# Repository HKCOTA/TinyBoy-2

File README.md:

# TinyBoy(TM) 2
A 3D Printer for Kids.

This repo are stored all the Blue Prints and design diagrams.
The TinyBoy design comes ABSOLUTELY NO WARRANTY!

[TinyBoy(TM) 2](http://www.tinyboy.net) by [Hong Kong Creative Open Technology Association (HKCOTA)](http://cota.hk), blueprints and designs are licensed under a Creative Commons Attribution-NonCommercial-ShareAlike 4.0 International (CC BY-NC-SA 4.0).
  
To view a copy of this license, visit [https://creativecommons.org/licenses/by-nc-sa/4.0/legalcode](https://creativecommons.org/licenses/by-nc-sa/4.0/legalcode). 

# You are free to:

* Share — copy and redistribute the material in any medium or format
* Adapt — remix, transform, and build upon the material 

# Under the following terms:

* Attribution — You must give appropriate credit, provide a link to the license, and indicate if changes were made. You may do so in any reasonable manner, but not in any way that suggests the licensor endorses you or your use.

* NonCommercial — You may not use the material for commercial purposes.

* ShareAlike — If you remix, transform, or build upon the material, you must distribute your contributions under the same license as the original. 

# TinyBoy Projects are also using the hardware and firmware from the following projects:

## Melzi Projects, For L10/L16
* using MKS's Melzi clone board, SMELZI, which should be license under GPL 2.0. MKS said it is possible to get the board design if you ask them. But we have doubt on it.
The printers produced by MakeOmnia Ltd would still use this board. 

## RMAPS v1.4, For Lite/J10
* which is license under GPL. As HKCOTA have doubt on the board, so for the HKCOTA version, we choose to use RAMPS v1.4 + Arduino as the main board of the printer.

## Marlin Firmware project
* which is license under GPL. You can get the forked source from [https://github.com/wanleung/Marlin-TinyBoy/](https://github.com/wanleung/Marlin-TinyBoy/).

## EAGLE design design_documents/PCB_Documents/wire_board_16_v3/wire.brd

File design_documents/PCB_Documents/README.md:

# TinyBoy(TM) 2
A 3D Printer for Kids.

This repo are stored all the Blue Prints and design diagrams.
The TinyBoy design comes ABSOLUTELY NO WARRANTY!

[TinyBoy(TM) 2](http://www.tinyboy.net) by [Hong Kong Creative Open Technology Association (HKCOTA)](http://cota.hk) is licensed under a Creative Commons Attribution-NonCommercial-ShareAlike 4.0 International (CC BY-NC-SA 4.0).
  
To view a copy of this license, visit [https://creativecommons.org/licenses/by-nc-sa/4.0/legalcode](https://creativecommons.org/licenses/by-nc-sa/4.0/legalcode). 

# You are free to:

* Share — copy and redistribute the material in any medium or format
* Adapt — remix, transform, and build upon the material 

# Under the following terms:

* Attribution — You must give appropriate credit, provide a link to the license, and indicate if changes were made. You may do so in any reasonable manner, but not in any way that suggests the licensor endorses you or your use.

* NonCommercial — You may not use the material for commercial purposes.

* ShareAlike — If you remix, transform, or build upon the material, you must distribute your contributions under the same license as the original.

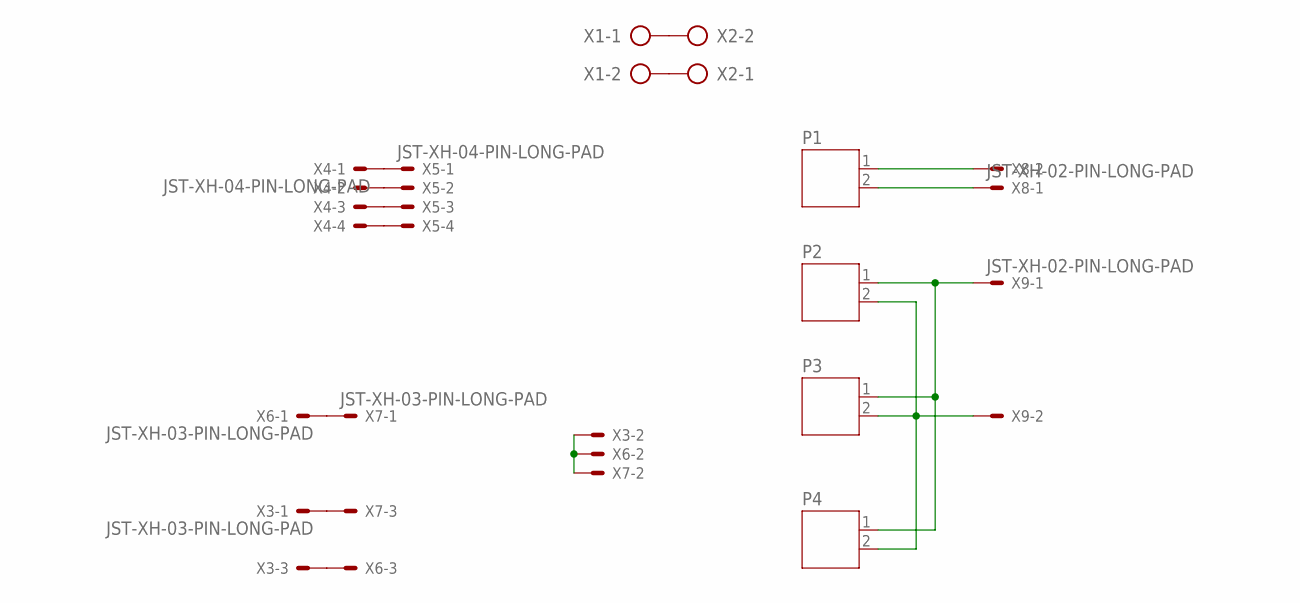
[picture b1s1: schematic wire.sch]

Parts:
P1, P2, P3, P4: JST-PH2
X1, X2: AK500/2
X3, X6, X7: JST-XH-03-PIN-LONG-PAD; JST-XH-03-PACKAGE-LONG-PAD
X4, X5: JST-XH-04-PIN-LONG-PAD; JST-XH-04-PACKAGE-LONG-PAD
X8, X9: JST-XH-02-PIN-LONG-PAD; JST-XH-02-PACKAGE-LONG-PAD

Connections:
unnamed: X4.1, X5.1
unnamed: P2.1, P3.1, P4.1, X9.1
unnamed: X4.2, X5.2
unnamed: X4.3, X5.3
unnamed: X4.4, X5.4
unnamed: P2.2, P3.2, P4.2, X9.2
unnamed: X1.1, X2.2
unnamed: X1.2, X2.1
unnamed: P1.1, X8.2
unnamed: P1.2, X8.1
unnamed: X6.1, X7.1
unnamed: X3.2, X6.2, X7.2
unnamed: X3.1, X7.3
unnamed: X3.3, X6.3

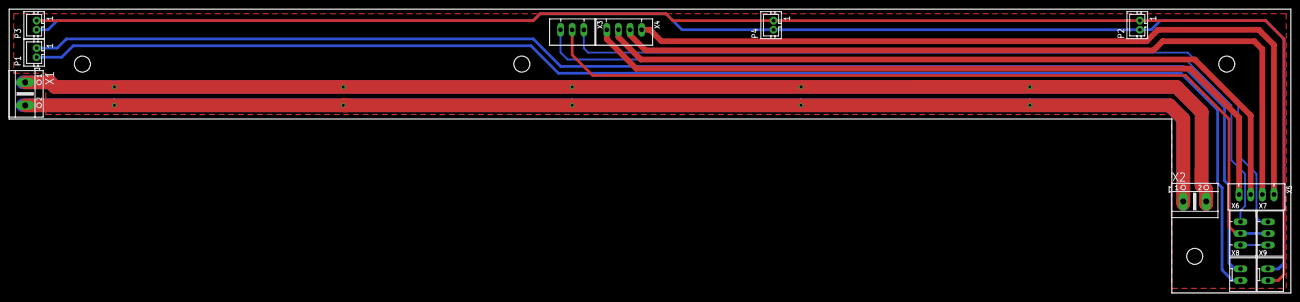
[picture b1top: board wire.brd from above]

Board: 2 copper layers, 280.0 x 62.0 mm, 13 parts (0 on the bottom side), 14 nets.

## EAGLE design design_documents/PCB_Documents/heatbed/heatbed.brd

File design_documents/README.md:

# TinyBoy(TM) 2
A 3D Printer for Kids.

This repo are stored all the Blue Prints and design diagrams.
The TinyBoy design comes ABSOLUTELY NO WARRANTY!

[TinyBoy(TM) 2](http://www.tinyboy.net) by [Hong Kong Creative Open Technology Association (HKCOTA)](http://cota.hk), blueprints and designs are licensed under a Creative Commons Attribution-NonCommercial-ShareAlike 4.0 International (CC BY-NC-SA 4.0).
  
To view a copy of this license, visit [https://creativecommons.org/licenses/by-nc-sa/4.0/legalcode](https://creativecommons.org/licenses/by-nc-sa/4.0/legalcode). 

# You are free to:

* Share — copy and redistribute the material in any medium or format
* Adapt — remix, transform, and build upon the material 

# Under the following terms:

* Attribution — You must give appropriate credit, provide a link to the license, and indicate if changes were made. You may do so in any reasonable manner, but not in any way that suggests the licensor endorses you or your use.

* NonCommercial — You may not use the material for commercial purposes.

* ShareAlike — If you remix, transform, or build upon the material, you must distribute your contributions under the same license as the original. 

# TinyBoy Projects are also using the hardware and firmware from the following projects:

## Melzi Projects, For L10/L16
* using MKS's Melzi clone board, SMELZI, which should be licensed under GPL 2.0. MKS said it is possible to get the board design if you ask them. But we have doubt on it.
The printers, which are produced by MakeOmnia Ltd., would still use this board. The version L10/L16 are supported by MakeOmnia Ltd. only.  

## RMAPS v1.4, For Lite/J10
* which is licensed under GPL. As HKCOTA have doubt on the board, so for the HKCOTA version, we choose to use RAMPS v1.4 + Arduino as the main board of the printer. And it would be supported by HKCOTA and its community.

## Marlin Firmware project
* which is licensed under GPL. You can get the forked source from [https://github.com/wanleung/Marlin-TinyBoy/](https://github.com/wanleung/Marlin-TinyBoy/).

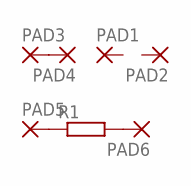
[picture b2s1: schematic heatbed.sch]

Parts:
PAD1, PAD2, PAD3, PAD4, PAD5, PAD6: SMD5; SMD2,54-5,08
R1: R-EU_R0805; R0805

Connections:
unnamed: PAD5.1, R1.1
unnamed: PAD6.1, R1.2
unnamed: PAD3.1, PAD4.1

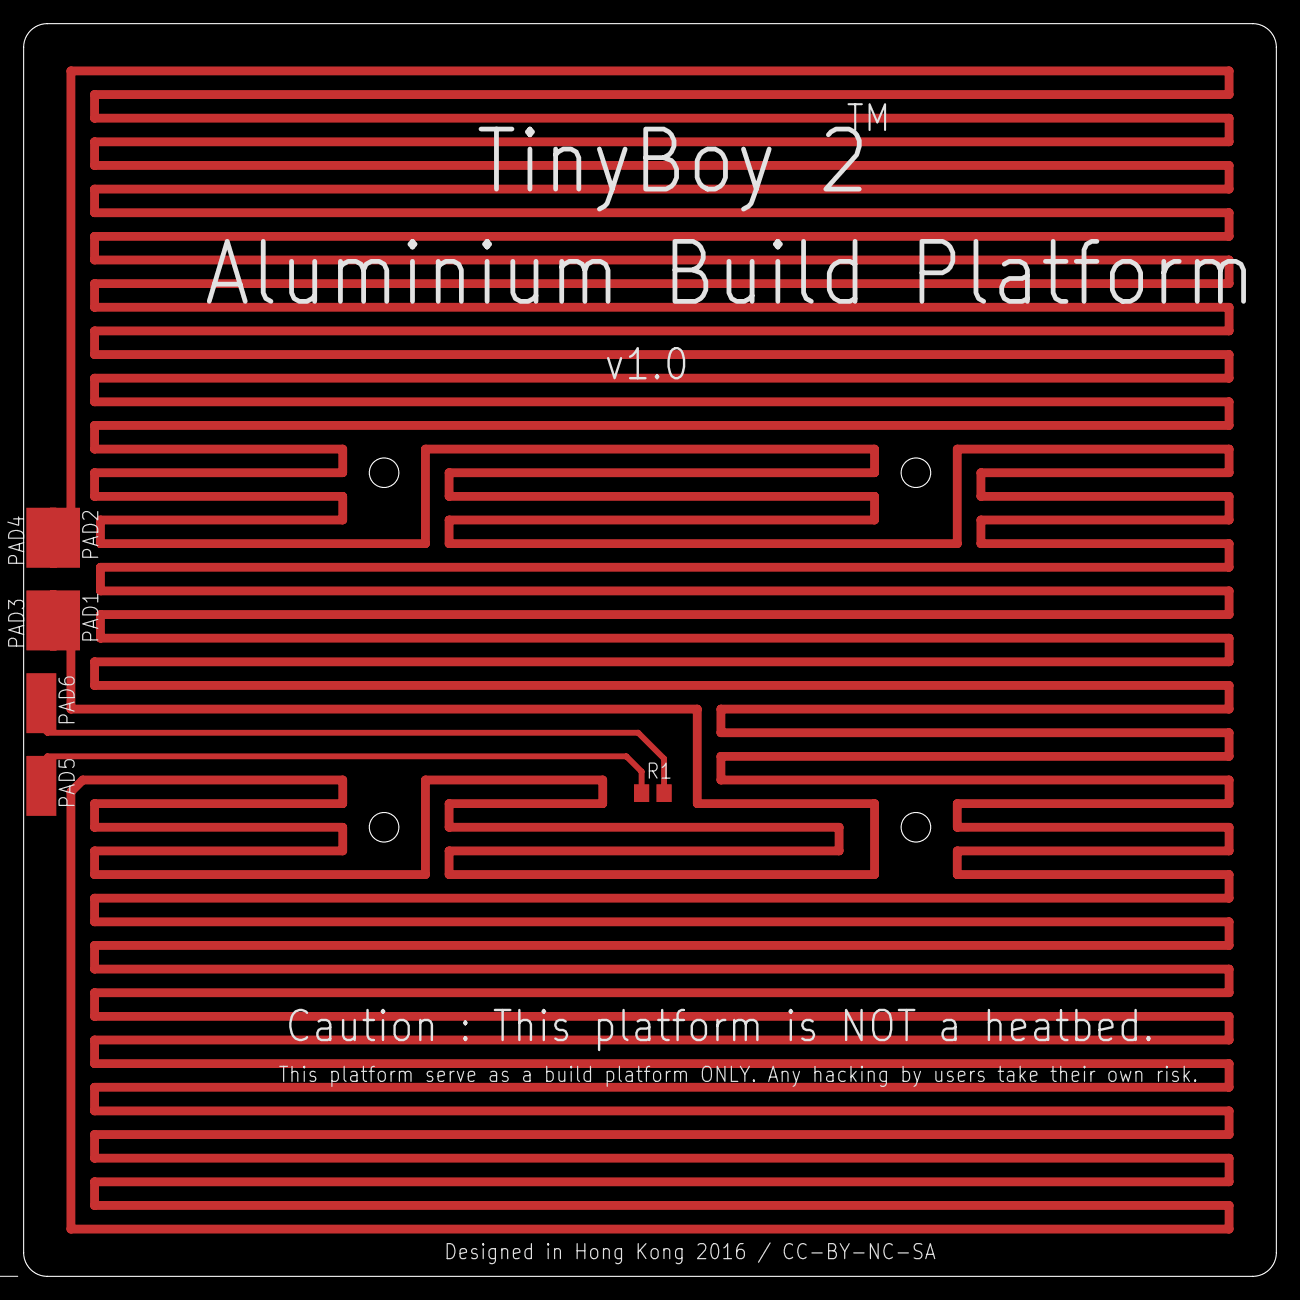
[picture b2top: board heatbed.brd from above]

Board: 2 copper layers, 106.0 x 106.0 mm, 7 parts (0 on the bottom side), 3 nets.

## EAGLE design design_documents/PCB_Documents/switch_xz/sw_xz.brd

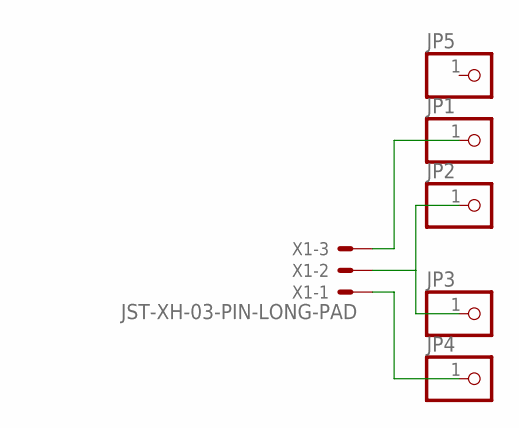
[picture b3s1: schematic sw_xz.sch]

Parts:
JP1, JP2, JP3, JP4, JP5: PINHD-1X1; 1X01
X1: JST-XH-03-PIN-LONG-PAD; JST-XH-03-PACKAGE-LONG-PAD

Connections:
unnamed: JP1.1, X1.3
unnamed: JP2.1, JP3.1, X1.2
unnamed: JP4.1, X1.1

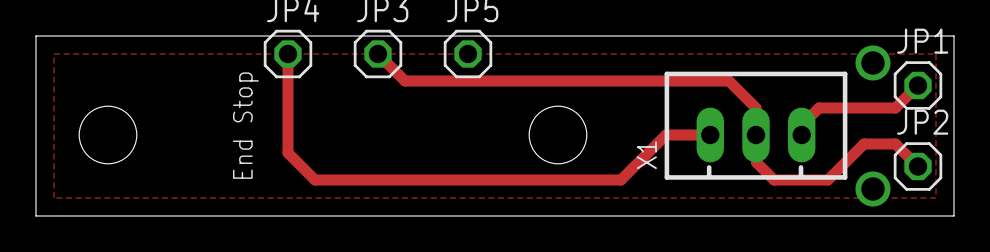
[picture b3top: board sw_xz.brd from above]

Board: 2 copper layers, 51.0 x 10.0 mm, 6 parts (0 on the bottom side), 3 nets.

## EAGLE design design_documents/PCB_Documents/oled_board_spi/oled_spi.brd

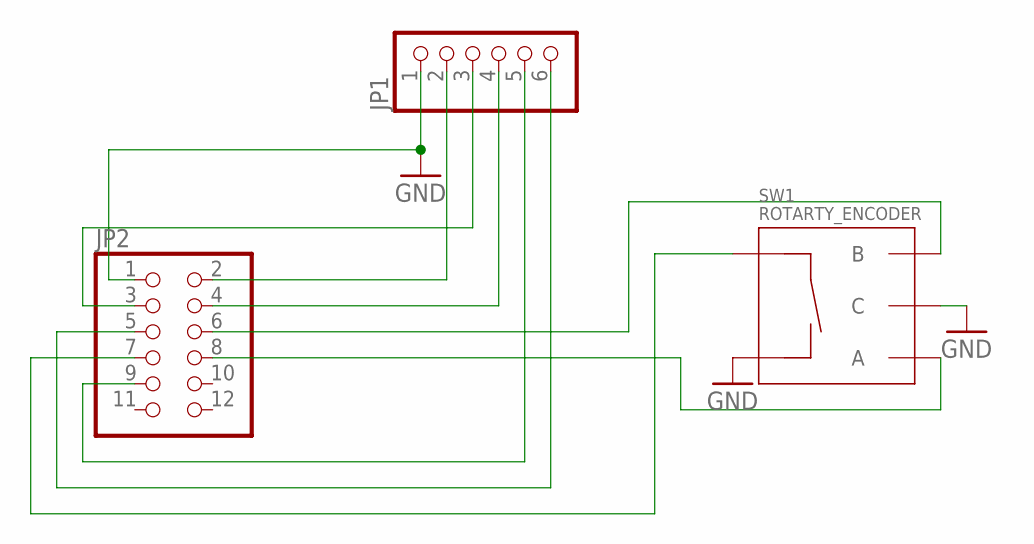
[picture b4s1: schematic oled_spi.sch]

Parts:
JP1: PINHD-1X6; 1X06
JP2: PINHD-2X6; 2X06
SW1: ROTARTY_ENCODER; ROTARY_ENC_PLAIN

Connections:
GND: JP1.1, JP2.1, SW1.C, SW1.SW-
unnamed: JP2.7, SW1.SW+
unnamed: JP1.2, JP2.2
unnamed: JP1.3, JP2.3
unnamed: JP1.4, JP2.4
unnamed: JP1.5, JP2.9
unnamed: JP2.6, SW1.B
unnamed: JP2.8, SW1.A
unnamed: JP1.6, JP2.5

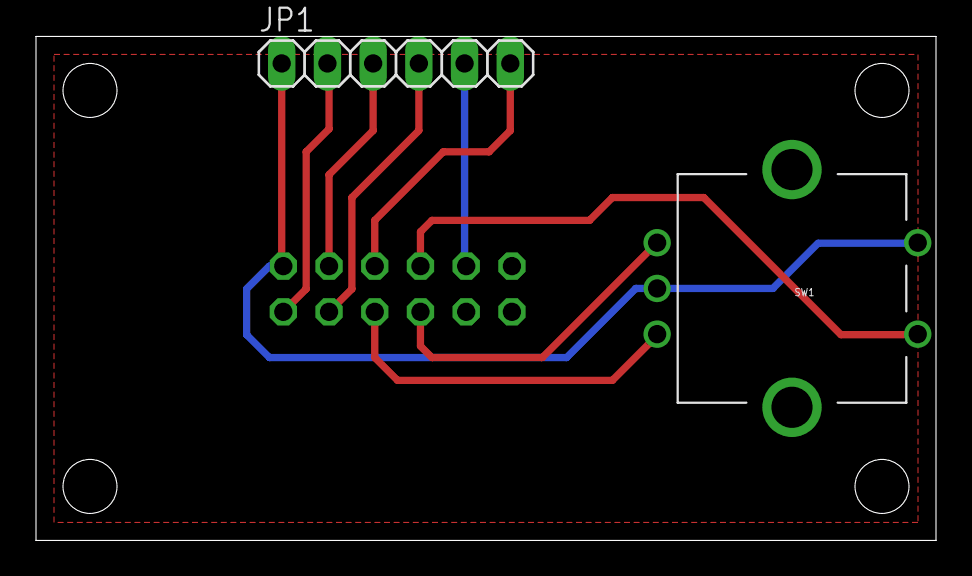
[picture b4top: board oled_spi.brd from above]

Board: 2 copper layers, 50.0 x 28.0 mm, 3 parts (1 on the bottom side), 9 nets.

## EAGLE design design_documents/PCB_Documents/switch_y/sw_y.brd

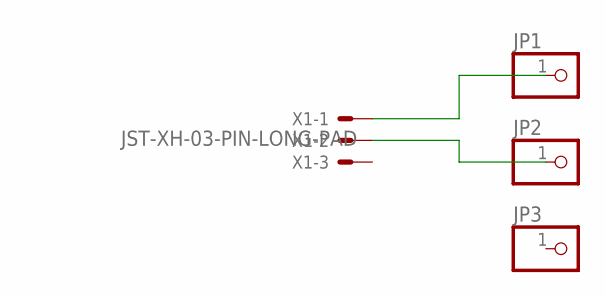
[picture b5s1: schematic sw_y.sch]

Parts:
JP1, JP2, JP3: PINHD-1X1; 1X01
X1: JST-XH-03-PIN-LONG-PAD; JST-XH-03-PACKAGE-LONG-PAD

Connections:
unnamed: JP1.1, X1.1
unnamed: JP2.1, X1.2

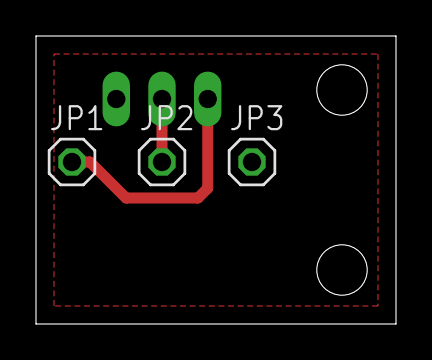
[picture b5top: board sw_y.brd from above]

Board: 2 copper layers, 20.0 x 16.0 mm, 4 parts (1 on the bottom side), 2 nets.

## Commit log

2016-10-21 Add new files
2016-10-21 Add new testing frameware
2016-10-22 typo
2016-11-22 Create L16
2016-12-03 Add readme
2016-12-03 Add L16 Firmware
2016-12-13 Add user guide
2016-12-19 Add J10(Lite) version
2018-02-10 Add L10/L16 Opensource Documents
2018-02-10 Add License Documents
2018-02-10 Correct to the right license info of the firmware and the main board
2018-02-10 Add RAMPS v1.4 board.
2018-02-10 Add firmware README
2018-02-10 update info for the boards

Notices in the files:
design_documents/PCB_Documents/heatbed/heatbed.brd:
Designed in Hong Kong 2016 / CC-BY-NC-SA
parts and their libraries:
SparkFun-Electromechanical: Licensing: Creative Commons ShareAlike 4.0 International - https://creativecommons.org/licenses/by-sa/4.0
